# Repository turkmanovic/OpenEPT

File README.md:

# Energy Profiler Toolset
Easy-to-use, low-cost, open-source solution that includes compatible hardware and software sets of tools. This comprehensive solution is designed to fulfill the need for firmware energy profiling, as well as State of Charge (SoC) and State of Health (SoH) algorithm evaluation for real LiPo battery-powered embedded devices.

Official product website 
[OpenEPT](https://openept.net/)

Official [youtube](https://www.youtube.com/playlist?list=PLTG-EoxvlLos_3Sex3R0yfDCwpDYyRSOo) channel 

# Supported by

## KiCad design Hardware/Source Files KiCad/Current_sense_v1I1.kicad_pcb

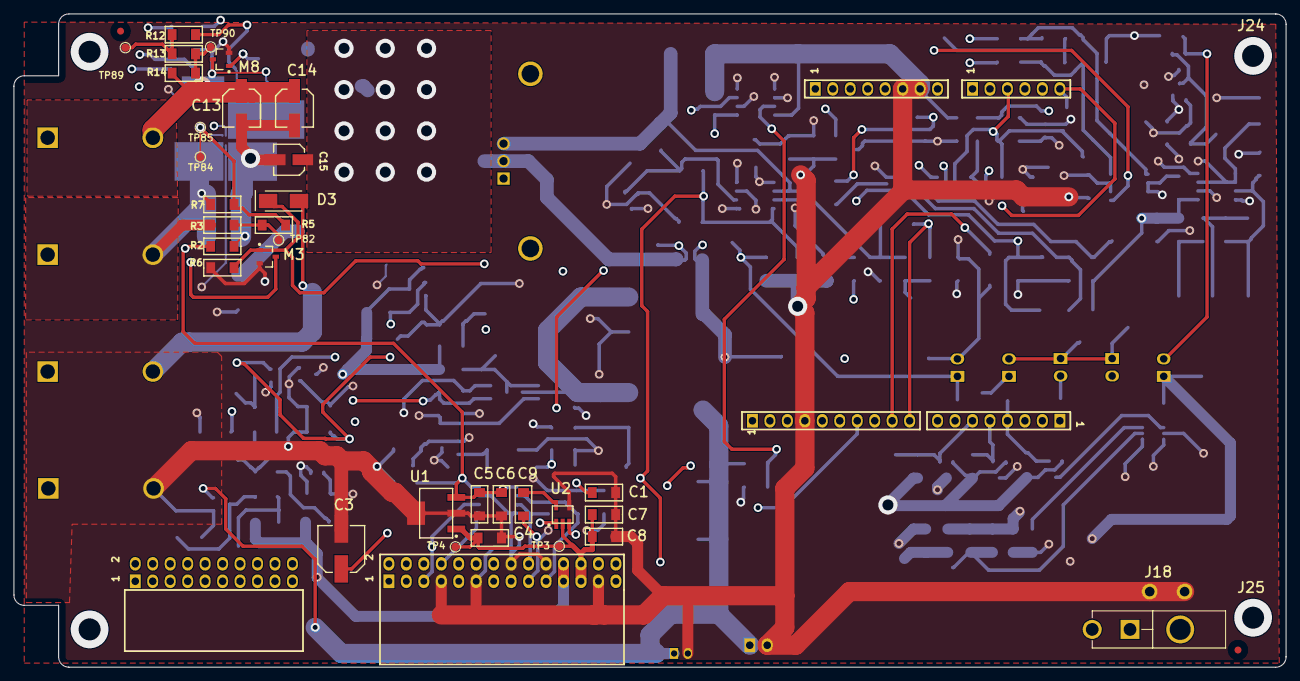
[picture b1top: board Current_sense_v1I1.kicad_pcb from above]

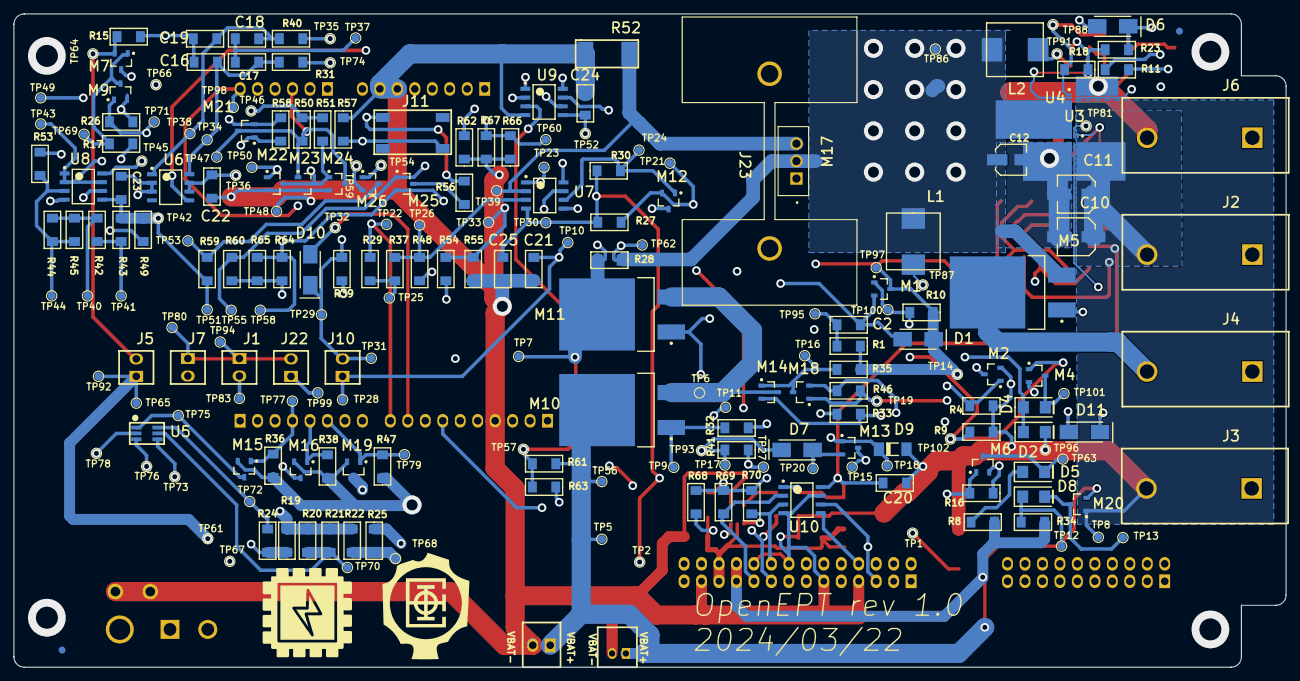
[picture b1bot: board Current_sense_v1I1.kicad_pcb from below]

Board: 4 copper layers, 185.0 x 95.0 mm, 273 parts (228 on the bottom side), 97 nets.

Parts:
C1, C8, C9: 1uF; 1206Capacitor
C2: 3.3nF; 1206Capacitor
C3: 100uF/25V; CAPAE7366X60N
C4: 0.47uF; 1206Capacitor
C5, C6, C7, C20, C21, C22, C23, C24, C25: 100n; 1206Capacitor
C10, C11, C13, C14: 22uF/16V
C12, C15: 10uF/16V; 10uF/16V Electrolytic
C16, C17, C18, C19: 2.2n; 1206Capacitor
D1, D3, D6, D7, D10, D11: SS14; DIOM5026X23N
D2, D4, D8: Red; RED
D5: Green; GREEN
D9: 3V3 Zener; DIOMELF3515N
FM1, FM2: Fiducial marker; Fiducal Marker
J1, J5, J7, J10, J22: 2_PIN_254; 2_PIN_2.54mm
J2, J4, J6: Red Connector; RED CONNECTOR
J3: Black Connector; BLACK CONNECTOR
J8: Battery connector clamp; 2.54mm CLAMP connector
J9: PH2.0 battery connector; PH2.0 connector
J11: Push Button; PUSH_BUTTON
J12: 6 pin 2.54 mm male; 6_pin_header_male_2_54
J13: 10 pin male 2.54mm pitch; 10_pin_header_male_2_54
J14: 20 pin 2.54 male straight; 20_pin_header_angled_female_2_54_mm
J15: 8 pin 2.54 male header; 8_pin_header_male_2_54
J16: 28 pin male right angle; 28_PIN_HEADER_RIGHT_ANGLE
J17: power 8 pin; 8_pin_header_male_2_54
J18: 4907; 4907_FOOTPRINT
J19, J20, J24, J25: PCB-MB-01
J21: 39-10-1020; 39-30-1020
J23: Heat Sink; HEAT_SINK
L1, L2: 1uH; PA4333_7.4x6.8x3.2mm
M1, M7, M13: TSM500P02CX RFG; SOT95P240X100-3N
M2, M3, M4, M6, M8, M9, M12, M14, M15, M16, M18, M19, M20, M21, M22, M23, M24: 2N7002L; SOT95P240X100-3N
M5, M10, M11: IRF4905STRLPBF; DPAK254P1524X483-3L
M17: TK4R3E06PL,S1X; TO-220-3
M25, M26: TSM250N02CX RFG; SOT95P240X100-3N
R1, R19, R22, R24, R25, R31, R40: 220; RESISTOR1206
R2, R11, R14, R26, R39, R44, R45, R50, R51, R53, R54, R55, R57, R58, R60, R62, R63, R68, R69, R70: 10k; RESISTOR1206
R3: 56k; RESISTOR1206
R4, R6, R7, R9, R18, R23, R27, R30, R32, R35, R36, R38, R46, R47, R49: 100k; RESISTOR1206
R5: 680k; RESISTOR1206
R8, R10, R34: 560; RESISTOR1206
R12, R13: 220k; RESISTOR1206
R15, R17, R41: 33k; RESISTOR1206
R16: 1M; RESISTOR1206
R20, R21, R37, R43, R48: 1k; RESISTOR1206
R28: 45mOhm; RESISTOR1206
R29: 6.8k; RESISTOR1206
R33, R42, R64, R65, R66, R67: 100; RESISTOR1206
R52: 75mOhm; RESISTOR2512
R56, R59: 10; RESISTOR1206
R61: 3.3k; RESISTOR1206
TP1, TP2, TP3, TP4, TP5, TP6, TP7, TP8, TP9, TP10, TP11, TP12, TP13, TP14, TP15, TP16, TP17, TP18, TP19, TP20, TP21, TP22, TP23, TP24, TP25, TP26, TP27, TP28, TP29, TP30, TP31, TP32, TP33, TP34, TP35, TP36, TP37, TP38, TP39, TP40, TP41, TP42, TP43, TP44, TP45, TP46, TP47, TP48, TP49, TP50, TP51, TP52, TP53, TP54, TP55, TP56, TP57, TP58, TP59, TP60, TP61, TP62, TP63, TP64, TP65, TP66, TP67, TP68, TP69, TP70, TP71, TP72, TP73, TP74, TP75, TP76, TP77, TP78, TP79, TP80, TP81, TP82, TP83, TP84, TP85, TP86, TP87, TP88, TP89, TP90, TP91, TP92, TP93, TP94, TP95, TP96, TP97, TP98, TP99, TP100, TP101, TP102: TestPoint
U1: 3V3 Regulator; SOT230P700X180-4N
U2: TPS60400; SOT95P280X135-5N
U3, U4: TPS61023DRLR; SOT563
U5: RGB diode; RGBDIODE
U6: INA296A1SOIC8; SOIC127P600X175-8N
U7, U8, U9: LM358DR; SOIC127P600X175-8N
U10: M24C32-WMN6P; SOIC127P600X175-8N

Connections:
3V3: C3.1, C5.2, C6.2, C20.2, C22.1, J1.1, J7.1, J22.2, R2.2, R11.2, R54.2, R68.2, R69.2, R70.2, TP1.1, TP36.1, TP80.1, TP94.1, U1.3, U6.6, U6.7, U10.8
3V3_FOR_OUT: C13.1, C14.1, J6.2, R14.2, U4.6
3V3_FOR_OUT_DISABLE: D6.1, J15.8
5V: C4.2, C7.2, C8.2, C23.1, J11.4, J16.23, J16.24, R43.1, R49.2, R50.2, R51.2, R56.2, R59.2, TP3.1, TP4.1, TP42.1, TP46.1, TP51.1, U1.1, U2.2, U8.5
5V_FOR_OUT: C10.1, C11.1, J2.2, R3.2, U3.6
5V_FOR_OUT_DISABLE: D3.1, J15.7
12V: C21.2, C24.2, D1.2, J5.1, J10.1, J16.21, J16.22, M1.3, M7.3, R1.1, R8.2, R10.1, R17.2, R19.2, R20.2, R21.2, R22.2, R34.2, R35.2, TP10.1, TP14.1, TP28.1, TP52.1, TP61.1, TP65.1, TP66.1, TP92.1, TP97.1, U7.5, U9.5
-5V: C1.1, C25.2, R27.1, R30.1, R41.1, TP2.1, TP27.1, TP30.1, U2.1, U7.4
CSA: J13.8, J16.9
DIB_RX: J15.2, J16.28
DIB_TX: J15.1, J16.27
GND: C1.2, C3.2, C4.1, C5.1, C6.1, C7.1, C8.1, C10.2, C11.2, C12.2, C13.2, C14.2, C15.2, C16.2, C19.1, C20.1, C21.1, C22.2, C23.2, C24.1, C25.1, D9.1, J3.2, J8.2, J9.2, J13.4, J16.7, J16.11, J16.16, J16.20, J16.25, J17.6, J17.7, J18.1, J18.2, M2.2, M3.2, M4.2, M6.2, M8.2, M9.2, M15.2, M16.2, M18.2, M19.2, M20.1, M21.2, M22.2, M23.2, M24.2, R4.1, R6.1, R7.1, R9.1, R15.1, R16.1, R18.1, R23.1, R26.1, R32.1, R36.1, R38.1, R39.1, R46.1, R47.1, R48.1, R52.1, R53.1, R55.1, R57.1, R58.1, R60.1, R62.1, R63.1, R64.1, R65.1, R66.1, R67.1, TP8.1, TP11.1, U1.2, U1.4, U2.4, U3.4, U4.4, U6.2, U6.3, U8.4, U9.4, U10.4, U10.7
GPIO_DAC: J13.10, R29.2, TP22.1
GPIO_DISABLE: D11.1, J12.6, M18.1, R46.2, TP19.1, TP98.1
I2C_ADDRESS_0: J16.17, R68.1, U10.1
I2C_ADDRESS_1: J16.19, R69.1, U10.2
I2C_ADDRESS_2: J16.18, R70.1, U10.3
LOAD_DISABLE: D10.1, J13.9, TP32.1
MISO: J13.6, J16.14
MOSI: J13.7, J16.15
NetC2_1: C2.1, R1.2, TP95.1
NetC2_2: C2.2, D1.1, D7.2, M1.2, M11.1, R41.2, TP17.1, TP93.1
NetC9_1: C9.1, U2.3
NetC9_2: C9.2, U2.5
NetC16_1: C16.1, C17.2, R31.2, TP34.1, U6.8
NetC17_1: C17.1, C18.2, TP37.1
NetC18_1: C18.1, C19.2, R40.2, TP38.1, U6.1
NetD2_1: D2.1, M2.3, TP96.1
NetD2_2: D2.2, D4.2, M1.1, R10.2, TP100.1
NetD3_2: D3.2, J1.2, M3.1, R6.2, TP83.1
NetD4_1: D4.1, M4.3, TP101.1
NetD5_1: D5.1, M6.3, TP63.1
NetD5_2: D5.2, R8.1
NetD6_2: D6.2, J7.2, M8.1, R23.2
NetD7_1: D7.1, M13.2, TP20.1
NetD8_1: D8.1, M20.3, TP13.1
NetD8_2: D8.2, R34.1, TP12.1
NetD9_2: D9.2, M13.1, R33.1, TP18.1
NetD10_2: D10.2, J10.2, R39.2, TP29.1, TP31.1, U7.7
NetD11_2: D11.2, J22.1, M2.1, R4.2, TP99.1
NetJ5_2: J5.2, M5.1, M7.2, R15.2, TP64.1
NetJ11_1: J11.1, M22.1, R57.2, TP50.1
NetJ12_3: J12.3, M26.2, R66.2, R67.2, TP59.1, TP60.1, U9.2
NetJ12_4: J12.4, M25.2, R64.2, R65.2, TP58.1, U9.7
NetL1_2: L1.2, TP87.1, U3.5
NetL2_2: L2.2, TP91.1, U4.5
NetM3_3: M3.3, R2.1, TP81.1, U3.2
NetM6_1: M6.1, M11.4, R16.2, R28.2, R31.1, TP7.1, TP74.1
NetM7_1: M7.1, M9.3, R17.1, TP69.1
NetM8_3: M8.3, R11.1, U4.2
NetM10_1: M10.1, R32.2, TP9.1
NetM10_3: M10.3, M11.3, M14.3, TP6.1
NetM12_1: M12.1, R30.2, TP24.1, U7.6
NetM12_2: M12.2, M17.1, R27.2, TP21.1
NetM12_3: M12.3, TP23.1, U7.1
NetM13_3: M13.3, M14.2, R33.2, TP15.1
NetM14_1: M14.1, M18.3, R35.1, TP16.1
NetM15_3: M15.3, TP75.1, U5.1
NetM16_3: M16.3, TP76.1, U5.5
NetM17_3: M17.3, R52.2, TP39.1, U7.2
NetM19_3: M19.3, TP78.1, U5.3
NetM21_1: M21.1, R58.2, TP49.1, U8.6
NetM21_3: M21.3, M23.1, M24.3, R50.1, TP47.1
NetM25_1: M25.1, R60.2, TP55.1, U9.6
NetM25_3: M25.3, R56.1
NetM26_1: M26.1, R62.2, TP54.1, U9.1
NetM26_3: M26.3, R59.1, TP53.1
NetR3_1: R3.1, R5.2, TP82.1
NetR5_1: R5.1, R7.2, TP84.1, TP85.1, U3.1
NetR12_1: R12.1, R18.2, TP88.1, U4.1
NetR12_2: R12.2, R13.1, TP89.1
NetR13_2: R13.2, R14.1, TP90.1
NetR19_1: R19.1, R24.2, TP67.1
NetR20_1: R20.1, R21.1, TP70.1, U5.4
NetR22_1: R22.1, R25.2, TP68.1
NetR24_1: R24.1, TP72.1, U5.2
NetR25_1: R25.1, TP73.1, U5.6
NetR29_1: R29.1, R37.2, TP25.1
NetR37_1: R37.1, R48.2, TP26.1, U7.3
NetR42_1: R42.1, R44.2, R45.2, TP40.1
NetR42_2: R42.2, R43.2, TP41.1
NetR44_1: R44.1, R45.1, R53.2, TP44.1, U8.3
NetR49_1: R49.1, TP43.1, U8.1, U8.2, U8.7
NetR54_1: R54.1, R55.2, TP33.1, U7.8
NetR61_1: R61.1, R63.2, TP57.1, U9.3
NetTP45_1: TP45.1, U6.5, U8.8, U9.8
OVERCURRENT: M4.1, M22.3, M23.3, M24.1, R9.2, R51.1, TP48.1, TP102.1
SCL: J13.1, J16.5, U10.6
SCLK: J13.5, J16.13
SDA: J13.2, J16.8, U10.5
SYSTEM_BLUE: J15.4, M15.1, R36.2, TP77.1
SYSTEM_GREEN: J15.5, M16.1, R38.2
SYSTEM_RED: J15.6, M19.1, R47.2, TP79.1
VBAT: J8.1, J9.1, M10.4, M20.2, R61.2, TP5.1, TP56.1
VBAT_AFTER_SHUNT: C12.1, C15.1, L1.1, L2.1, M5.3, M17.2, R28.1, R40.1, TP35.1, TP62.1, TP86.1, U3.3, U4.3
VBAT_DISABLE: J15.3, M9.1, R26.2, TP71.1
VBAT_FOR_OUT: J4.2, M5.4

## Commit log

2023-09-09 Created basic project directories
2023-09-09 Added documentation DIR
2023-09-09 Create LICENSE
2023-09-09 Removed unused file
2023-09-09 Added NLNet foundation image
2023-11-03 Initial firmware structure added
2023-11-03 Debug folder deleted
2023-11-03 .gitignore updated
2023-11-04 framework with first sucessfull ping
2023-11-04 Ethernet Updated
2023-11-04 Initial version of configuration project added
2023-11-04 .settings file excluded
2023-11-04 Start to remove autogenerated stm32cube code
2023-11-05 Framework structure refactorization
2023-11-05 Service placeholders added
2023-11-05 stream start added
2023-11-06 Work in progress, not tested
2023-11-06 initial schematic for overvoltage protection
2023-11-06 Interrupt callback added
2023-11-06 EXTI Lines are added
2023-11-07 Initial version - no tested
2023-11-07 System layer tested
2023-11-07 Initial
2023-11-08 iperf added
2023-11-09 Minor changes
2023-11-09 Initial not tested version of UART driver
2023-11-10 Initial working version developed
2023-11-10 Logging added within network service
2023-11-11 Project recreated
2023-11-11 Build dir changed
2023-11-14 Added dewicewnd ui
2023-11-15 Added scalability
2023-11-17 add directory for schematics, and full circuit drawing
2023-11-18 Template for objects names change
2023-11-19 Changed LEs to Labels in Statistics layout
2023-11-19 Added images and resource.qrc
2023-11-19 Toolbar added, menubar fixed and project icon added
2023-11-19 User file changed and build removed from git tracking
2023-11-19 Charts added
2023-11-19 Advance options button added
2023-11-22 Added adddevicewnd.ui
2023-11-25 Advance configuration window added
2023-11-25 Profiles tables overview added
2023-11-25 Window icon changed
2023-11-25 Advance option push button position fixed
2023-11-25 Advance options fixxed
2023-11-26 Add Device window functionalities added
2023-11-26 Connected devices overview
2023-11-26 Remove device option added
2023-11-26 New style added
2023-11-27 Advance options variable rename following template
2023-12-02 Default options added for Combs and Lines
2023-12-03 add current sense circuit simulation for 5A load
2023-12-03 update schematic with input stage filter
2023-12-04 Cube file changed
2023-12-04 Default IP parameters changed
2023-12-28 Add signals and slots for device, path and acquisition options
2023-12-28 New files added
2023-12-29 First command sucessfully processed
2023-12-29 New commands added
2023-12-29 Ethernet patched
2023-12-29 Error state added
2023-12-29 Logging message added within control service
2023-12-30 Logging added
2023-12-30 Doxygen added and Control service commented
2023-12-30 Control link integrated
2023-12-30 Firmware control messages integrated withing GUI
2024-01-03 Link status detection added
2024-01-03 Work in progress
2024-01-03 Console Wnd Initial layout created
2024-01-03 Status link server added
2024-01-03 Two log message types added
2024-01-04 Console wnd layout update and base functionalities added
2024-01-04 Status link message support added
2024-01-04 Status Link logic created inside firmware
2024-01-04 Send messages over status link added
2024-01-04 Control service comments updated
2024-01-18 Initial working version after Haris
2024-01-23 Console image and button added, updated consolewnd sig and slot naming
2024-02-13 Resolution change functionalities implemented
2024-02-13 Pro User file
2024-02-14 Git ignore file modified
2024-02-14 First compile
2024-02-14 First sucessfully compile after merging with gui_control
2024-02-15 Resolution configuration setting modified
2024-02-15 .launch files excluded from git tracking
2024-02-15 ADC3 configured inside config project to sync with Timer1
2024-02-15 Clock div and Sample time change functionalities implemented
2024-02-15 ADC Framework (Proof of Convept)
2024-02-16 Toggling led added
2024-02-16 Acquisition status added
2024-02-16 Basic control commands added
2024-02-16 .pro file added
2024-02-16 After merging before removed chache
2024-02-16 Commands names updated
2024-02-16 .cproject returned
2024-02-16 .cproject returned and modified
2024-02-16 .cproject modified
2024-02-16 Undefined command supported
2024-02-16 Resolution, sampling time and clock div configuration added
2024-02-18 Initial ADC working version
2024-02-18 Basic control commands updated
2024-02-19 ADC Driver updated
2024-02-19 Initial stream framework
2024-02-19 ADC configuration within sstream service added
2024-02-21 First successfull configuration obtained
2024-02-23 Control logic added inside firmware
2024-02-23 Control logic added inside GUI
2024-02-23 Sampling time and clock div added
2024-02-23 Clock div and sampling time control added
2024-02-23 Clock div and sampling time control added inside GUI application
2024-02-23 Channels sampling time added inside sstream
2024-02-23 Channels sampling time control added inside firmware
2024-02-23 Channels sampling time control added inside GUI
2024-02-23 clock div fixed
2024-02-25 Voltage and current offset added
2024-02-25 Voltage and current offset control added inside AnalogIN
2024-02-25 Gloal configuration added
2024-02-25 Voltage and current control commands added
2024-02-25 Voltage and current offset control added inside GUI
2024-02-25 ADC Averaging ratio integrated inside Driver layer
2024-02-25 Averaging ration and clock control integrated inside sstream service
2024-02-25 Clock control and averaing ration control messages integrated
2024-02-25 Queue length increased
2024-02-25 Averaging ration default configuration implemented
2024-02-25 Averaging ratio and clock control integrated inside GUI
2024-02-25 Stream start option added inside stream service
2024-02-25 Stream start control messages added
2024-02-25 Commands history added
2024-02-25 Start and stop acqusition controls added
2024-02-25 Console icon modified
2024-02-25 Console style modified
2024-02-25 Code refactorized
2024-02-25 Obtained configuration is integrated into GUI fields
2024-02-25 sid identification added
2024-02-26 Gui Control update
2024-02-26 Unused signals and slots removed
2024-02-27 Refresh button function add, minor fixes and refactoring
2024-03-03 Acquisiton device commands list documentation
2024-03-13 Root patsh resolved
2024-04-02 add source files for Altium, BOM and pdf
2024-04-05 add block diagram (work in progress)
2024-04-08 update block diagram
2024-04-08 update block scheme
2024-05-02 IP Address configuration changed
2024-05-03 Ethernet bug fixed
2024-05-03 UDP connection to stream server added
2024-05-03 Stream task added as separate
2024-05-03 Ethernet fixed
2024-05-04 Initial streaming
2024-05-04 packet counter and magic number added
2024-05-05 Averaging option added
2024-05-05 Max number of samples buffers configured
2024-05-05 statistic added
2024-05-05 Sampling period and double buffer mode added
2024-05-05 Sampling period sucessfully added inside gui
2024-05-06 Delta t added on plot and also stream control updated
2024-05-06 Consumption type selection
2024-05-14 Write to file added
2024-05-24 add kicad source files, delete altium source files
2024-05-28 Data processing
2024-05-28 CMSIS updated
2024-05-28 Increased UDP buffer
2024-05-30 File processing error fixed
2024-05-30 Remove part of the code
2024-05-30 Maximized window option added
2024-06-04 Initial streaming version completed
2024-06-23 add defines in globalConfig.h
2024-06-23 add first draft of Energy Debugger
2024-06-27 non working commit
2024-06-27 Marcos add
2024-06-30 create SPI directory, and add spi source and header files
2024-06-30 enable SPI
2024-06-30 add spi driver
2024-08-03 Firmware modified
2024-08-03 GUI modified to print EBP info
2024-08-03 ENV variables modified
2024-08-03 Notify task mechanism added
2024-09-18 Scatter added
2024-09-20 Breakpoint names added
2024-09-29 EnergyPoint initial version
2024-10-03 Read ADC, RGB control and DAC control addded
2024-10-03 Font size added and autocomplete
2024-10-03 Console elements added
2024-10-03 Graphic elements fixed
2024-10-04 Discharge control added
2024-10-07 Config project upgraded to support SPI
2024-10-10 Initial working version of ADC
2024-10-10 Driver modified to satisfy naming convention - SPI left
2024-10-10 SPI Driver refactorized
2024-10-10 Read registers added
2024-10-17 Initial version of new ADC added
2024-10-17 Project path changed and declaration moved
